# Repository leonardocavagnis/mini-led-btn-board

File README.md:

# Mini LED BTN Board

KiCad 9 project for an LED + Button board.  
Includes PCB and schematic files, as well as resources for testing and production.

## Repository Structure

### Folders

- `production/`: contains Gerber files, drill files, and everything needed to send the board to a PCB manufacturer.  
- `test/`: contains an Arduino sketch to test the board's functionality.

### KiCad Files

- `mini_led_button.kicad_pro` → main KiCad project file  
- `mini_led_button.kicad_sch` → schematic  
- `mini_led_button.kicad_pcb` → PCB layout  
- `mini_led_button.kicad_prl` → layer and print configuration  

## Usage

1. Open the `.kicad_pro` project in KiCad 9 to edit the schematic or PCB.  
2. Generate production files and save them in the `production/` folder.  
3. Upload the sketch from `test/` to an Arduino to verify the board functionality.

## Read More

For more details, see the related article: _coming soon..._

## Acknowledgements

Special thanks to [**PCBWay**](https://www.pcbway.com) for supporting this project and for PCB manufacturing.

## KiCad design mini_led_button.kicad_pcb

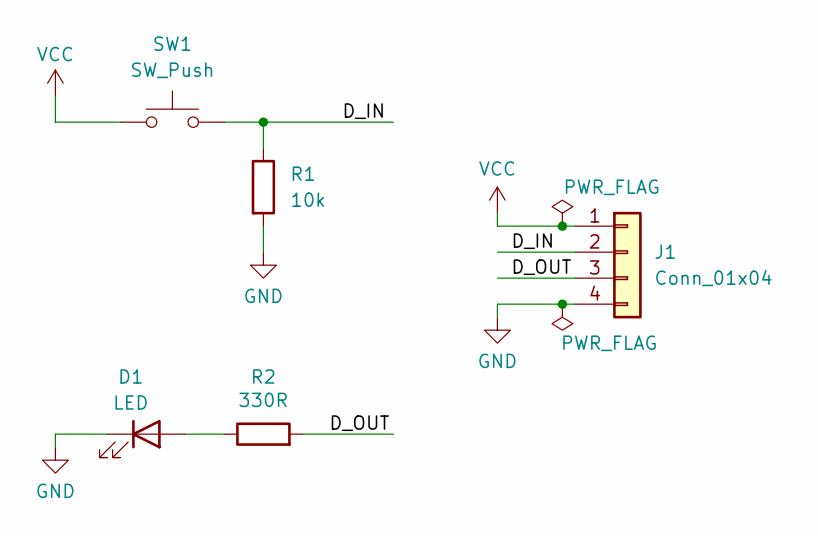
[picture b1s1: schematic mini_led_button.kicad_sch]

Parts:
D1: LED; LED_D3.0mm
J1: Conn_01x04; PinHeader_1x04_P2.54mm_Vertical
R1: 10k; R_Axial_DIN0207_L6.3mm_D2.5mm_P7.62mm_Horizontal
R2: 330R; R_Axial_DIN0207_L6.3mm_D2.5mm_P7.62mm_Horizontal
SW1: SW_Push; SW_PUSH_6mm

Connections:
/D_IN: J1.2, R1.1, SW1.2
/D_OUT: J1.3, R2.2
GND: D1.1 (K), J1.4, R1.2
unnamed: D1.2 (A), R2.1
VCC: J1.1, SW1.1

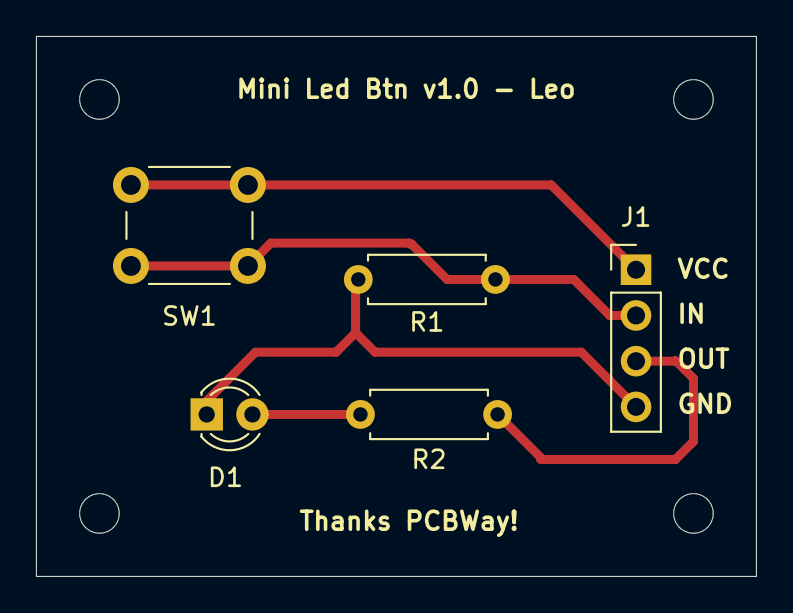
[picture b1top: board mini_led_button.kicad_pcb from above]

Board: 2 copper layers, 40.0 x 30.0 mm, 5 parts (0 on the bottom side), 5 nets.

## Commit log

2026-01-07 add KiCad project
2026-01-07 add gerber files
2026-01-07 add arduino test sketch
2026-01-07 Add README
2026-01-07 update readme with ack and img
